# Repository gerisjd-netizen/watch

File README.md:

# DIY Smartwatch

A DIY smartwatch built around the Seeed Studio XIAO ESP32-C3.

> **Status: work in progress.** The project is under active development, so features, wiring and the hardware layout may change.

## Features

- **Clock**: large HH:MM:SS display with the date shown smaller underneath.
- **Stopwatch**: start, stop and reset, with centisecond resolution.
- **Manual time setting**: set hour, minute, second, year, month and day from the Settings menu.
- **Accurate timekeeping**: an external DS3231 RTC chip keeps the time, even while the microcontroller sleeps.
- **Auto sleep**: after a period without button input, the display turns off and the microcontroller goes to sleep. Any button press wakes it up, and that press is ignored so it doesn't trigger an action by accident.

## Hardware

| Part | Notes |
|------|-------|
| Seeed Studio XIAO ESP32-C3 | Main microcontroller |
| SSD1306 128x64 OLED display | I2C |
| DS3231 RTC module | I2C, keeps the time |
| 3 push buttons | UP, OK, DOWN |
| Rechargeable battery | Connected directly, no power switch needed |

### Pinout

| Function | Pin |
|----------|-----|
| Button UP | GPIO 2 |
| Button OK | GPIO 3 |
| Button DOWN | GPIO 4 |
| I2C SDA | D4 |
| I2C SCL | D5 |

The buttons use the internal pull-up resistors, so wire each button between its pin and GND.

### Power

The battery can be connected directly. No power switch is required, because the microcontroller goes into sleep mode when no button input is detected for a while. Pressing any button wakes the watch up again.

### Physical layout

From the back of the watch to the front:

1. Flat Wi-Fi antenna
2. Battery
3. PCB
4. Display and buttons

> **Note:** the watch is **not waterproof** in any way. Keep it away from water.

## Controls

The watch has three buttons: **UP**, **OK** and **DOWN**.

| Button | Action |
|--------|--------|
| UP / DOWN | Switch between Clock, Stopwatch and Settings in the menu. Change values in Settings. Reset in the Stopwatch. |
| OK (short press) | Open the selected screen. Start/stop the stopwatch. Go to the next field in Settings. |
| OK (hold 3 s) | **Back**: exit the current screen to the menu. |

### Stopwatch

1. Select **STOPWATCH** with UP/DOWN and press OK to enter.
2. Press OK to start, press OK again to stop.
3. Press UP or DOWN to reset.
4. Hold OK for 3 seconds to leave.

### Setting the time

1. Select **SETTINGS** with UP/DOWN and press OK to enter.
2. Use UP/DOWN to change the value (hold for fast repeat) and OK to go to the next field: hour, minute, second, year, month, day.
3. Press OK on the last field (day) to save the time to the RTC.
4. Holding OK for 3 seconds exits without saving.

## Building

1. Install the [Arduino IDE](https://www.arduino.cc/en/software) with ESP32 board support, and select the XIAO ESP32-C3 board.
2. Install these libraries from the Library Manager:
   - `RTClib` (Adafruit)
   - `U8g2` (olikraus)
3. Open the sketch, then compile and upload.

If the RTC has lost power, it is set to the compile time on startup. After that, correct the time from the Settings menu.

## Configuration

These constants at the top of the sketch can be changed:

| Constant | Default | Meaning |
|----------|---------|---------|
| `SLEEP_AFTER_MS` | 60000 | Inactivity time before the display turns off and the microcontroller sleeps |
| `EXIT_HOLD_MS` | 3000 | How long to hold OK to go back |
| `DEBOUNCE_MS` | 30 | Button debounce time |

## Roadmap

This is an early version. More features are planned.

## License

MIT license

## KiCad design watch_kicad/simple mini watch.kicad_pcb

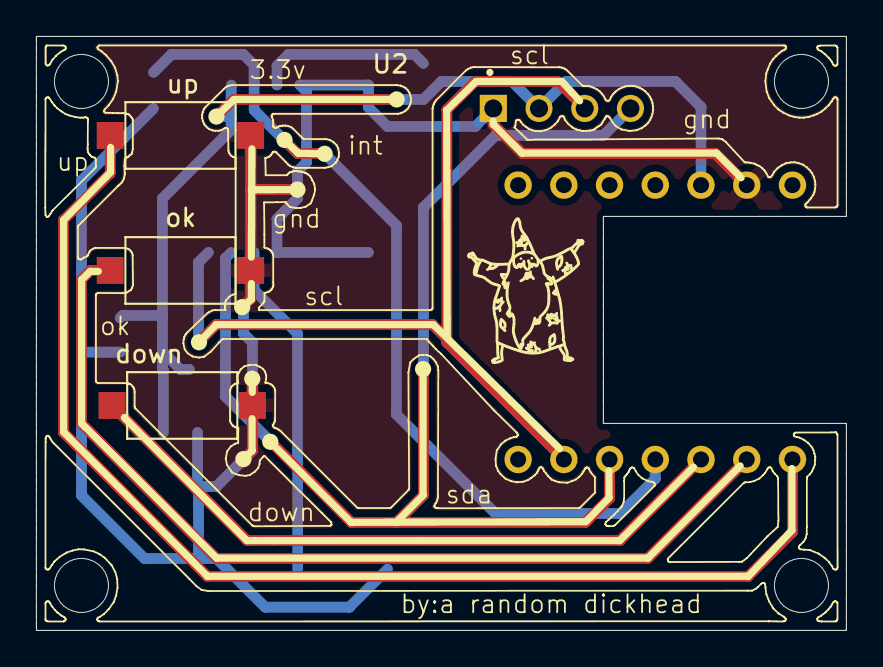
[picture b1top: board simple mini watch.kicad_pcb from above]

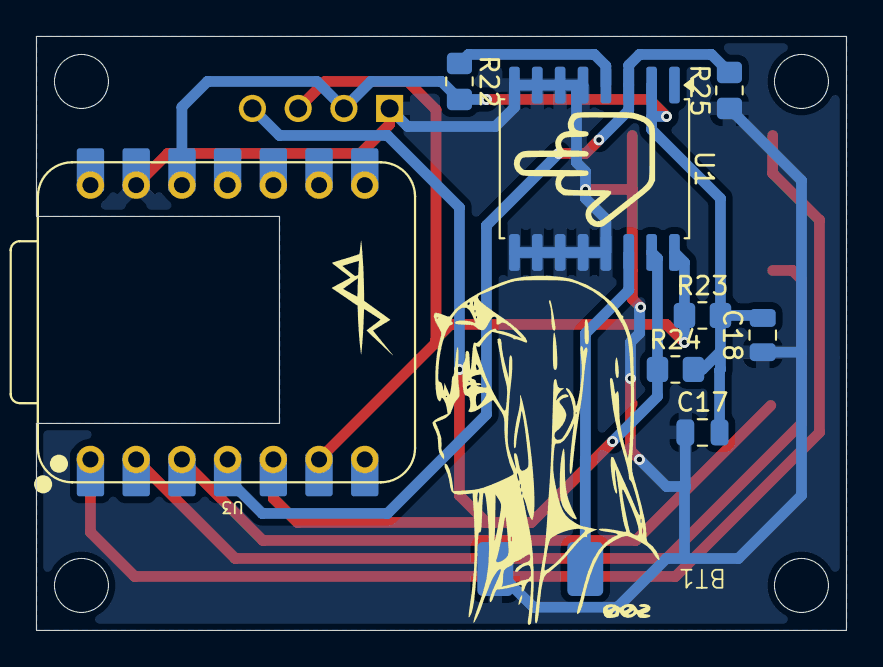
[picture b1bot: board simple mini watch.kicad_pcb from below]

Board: 2 copper layers, 45.0 x 33.0 mm, 13 parts (9 on the bottom side), 10 nets.

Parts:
BT1: Battery_Cell; Névtelen
C17: 100nF; C_0805_2012Metric
C18: 4.7uf; C_0805_2012Metric
R22, R25: 10k; R_0805_2012Metric_Pad1.20x1.40mm_HandSolder
R23, R24: 4.7k; R_0805_2012Metric_Pad1.20x1.40mm_HandSolder
U1: DS3231M; SOIC-16W_7.5x10.3mm_P1.27mm
U2: DM-OLED096-636; MODULE_DM-OLED096-636
U3: XIAO ESP32C3; XIAO-ESP32-C3-DIP
down: down; SW_SPST_CK_RS282G05A3
ok: ok; SW_SPST_CK_RS282G05A3
up: up; SW_SPST_CK_RS282G05A3

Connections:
3.3v: C17.2, C18.2, R22.2, R23.2, R24.2, U1.2 (VCC), U2.2 (VCC_IN), U3.12 (VCC_3V3)
unnamed: BT1.1 (+), U1.14 (VBAT)
unnamed: R22.1, U1.4 (~RST)
down: U3.3 (D2), down.1
int: R25.2, U1.3 (~INT/SQW), U3.4 (D3)
ok: U3.2 (D1), ok.1
scl: R23.1, U1.16 (SCL), U2.3 (SCL), U3.6 (D5)
sda: R24.1, U1.15 (SDA), U2.4 (SDA), U3.5 (D4)
sys_gnd: BT1.2 (-), C17.1, C18.1, R25.1, U1.5 (GND), U1.6 (GND), U1.7 (GND), U1.8 (GND), U1.9 (GND), U1.10 (GND), U1.11 (GND), U1.12 (GND), U1.13 (GND), U2.1 (GND), U3.13 (GND), down.2, ok.2, up.2
up: U3.1 (D0), up.1
